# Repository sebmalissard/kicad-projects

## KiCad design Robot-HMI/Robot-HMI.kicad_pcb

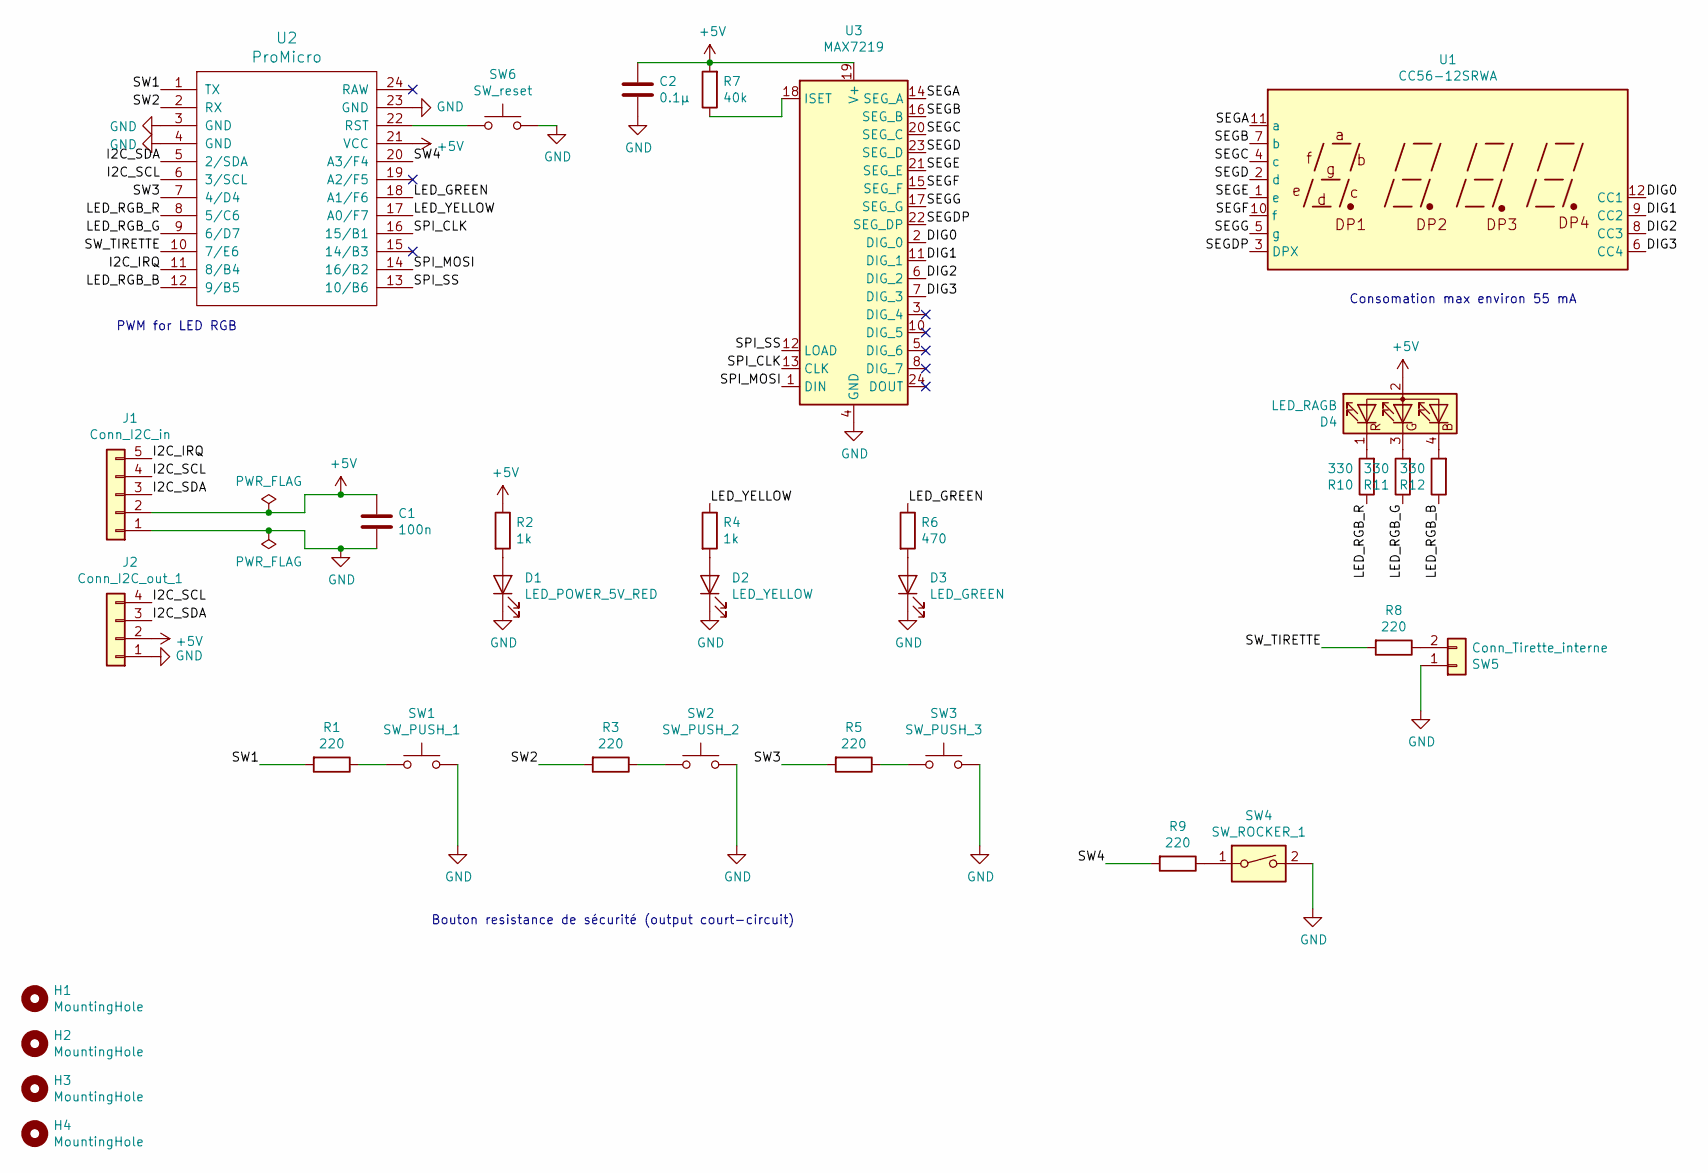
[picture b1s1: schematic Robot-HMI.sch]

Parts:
C1: 100n; C_Disc_D4.3mm_W1.9mm_P5.00mm
C2: 0.1µ; C_Disc_D4.3mm_W1.9mm_P5.00mm
D1: LED_POWER_5V_RED; LED_D5.0mm
D2: LED_YELLOW; LED_D5.0mm
D3: LED_GREEN; LED_D5.0mm
D4: LED_RAGB; LED_D5.0mm-4_RGB_Staggered_Pins
H1, H2, H3, H4: MountingHole; MountingHole_3.2mm_M3
J1: Conn_I2C_in; Molex_SL_171971-0005_1x05_P2.54mm_Vertical
J2: Conn_I2C_out_1; Molex_SL_171971-0004_1x04_P2.54mm_Vertical
R1, R3, R5, R8, R9: 220; R_Axial_DIN0207_L6.3mm_D2.5mm_P7.62mm_Horizontal
R2, R4: 1k; R_Axial_DIN0207_L6.3mm_D2.5mm_P7.62mm_Horizontal
R6: 470; R_Axial_DIN0207_L6.3mm_D2.5mm_P7.62mm_Horizontal
R7: 40k; R_Axial_DIN0207_L6.3mm_D2.5mm_P7.62mm_Horizontal
R10, R11, R12: 330; R_Axial_DIN0207_L6.3mm_D2.5mm_P7.62mm_Horizontal
SW1: SW_PUSH_1; SW_PUSH_12mm_H4.5mm
SW2: SW_PUSH_2; SW_PUSH_12mm_H4.5mm
SW3: SW_PUSH_3; SW_PUSH_12mm_H4.5mm
SW4: SW_ROCKER_1; Molex_SL_70553-0001_1x02_P2.54mm_Horizontal
SW5: Conn_Tirette_interne; Molex_SL_70553-0001_1x02_P2.54mm_Horizontal
SW6: SW_reset; SW_PUSH_6mm_H9.5mm
U1: CC56-12SRWA; CA56-12SRWA
U2: ProMicro
U3: MAX7219; DIP-24_W7.62mm

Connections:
+5V: C1.1, C2.1, D4.2 (A), J1.2, J2.2, R2.1, R7.2, U2.21 (VCC), U3.19 (V+)
/DIG0: U1.12 (CC1), U3.2 (DIG_0)
/DIG1: U1.9 (CC2), U3.11 (DIG_1)
/DIG2: U1.8 (CC3), U3.6 (DIG_2)
/DIG3: U1.6 (CC4), U3.7 (DIG_3)
/I2C_IRQ: J1.5, U2.11 (8/B4)
/I2C_SCL: J1.4, J2.4, U2.6 (3/SCL)
/I2C_SDA: J1.3, J2.3, U2.5 (2/SDA)
/LED_GREEN: R6.1, U2.18 (A1/F6)
/LED_RGB_B: R12.1, U2.12 (9/B5)
/LED_RGB_G: R11.1, U2.9 (6/D7)
/LED_RGB_R: R10.1, U2.8 (5/C6)
/LED_YELLOW: R4.1, U2.17 (A0/F7)
/SEGA: U1.11 (a), U3.14 (SEG_A)
/SEGB: U1.7 (b), U3.16 (SEG_B)
/SEGC: U1.4 (c), U3.20 (SEG_C)
/SEGD: U1.2 (d), U3.23 (SEG_D)
/SEGDP: U1.3 (DPX), U3.22 (SEG_DP)
/SEGE: U1.1 (e), U3.21 (SEG_E)
/SEGF: U1.10 (f), U3.15 (SEG_F)
/SEGG: U1.5 (g), U3.17 (SEG_G)
/SPI_CLK: U2.16 (15/B1), U3.13 (CLK)
/SPI_MOSI: U2.14 (16/B2), U3.1 (DIN)
/SPI_SS: U2.13 (10/B6), U3.12 (LOAD)
/SW1: R1.2, U2.1 (TX)
/SW2: R3.2, U2.2 (RX)
/SW3: R5.2, U2.7 (4/D4)
/SW4: R9.2, U2.20 (A3/F4)
/SW_TIRETTE: R8.2, U2.10 (7/E6)
GND: C1.2, C2.2, D1.1 (K), D2.1 (K), D3.1 (K), J1.1, J2.1, SW1.2, SW2.2, SW3.2, SW4.2, SW5.1, SW6.2, U2.3 (GND), U2.4 (GND), U2.23 (GND), U3.4 (GND), U3.9 (GND)
unnamed: D1.2 (A), R2.2
unnamed: D2.2 (A), R4.2
unnamed: D3.2 (A), R6.2
unnamed: D4.1 (RK), R10.2
unnamed: D4.3 (GK), R11.2
unnamed: D4.4 (BK), R12.2
unnamed: R1.1, SW1.1
unnamed: R3.1, SW2.1
unnamed: R5.1, SW3.1
unnamed: R7.1, U3.18 (ISET)
unnamed: R8.1, SW5.2
unnamed: R9.1, SW4.1
unnamed: SW6.1, U2.22 (RST)

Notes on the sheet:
PWM for LED RGB
Consomation max environ 55 mA
Bouton resistance de sécurité (output court-circuit)

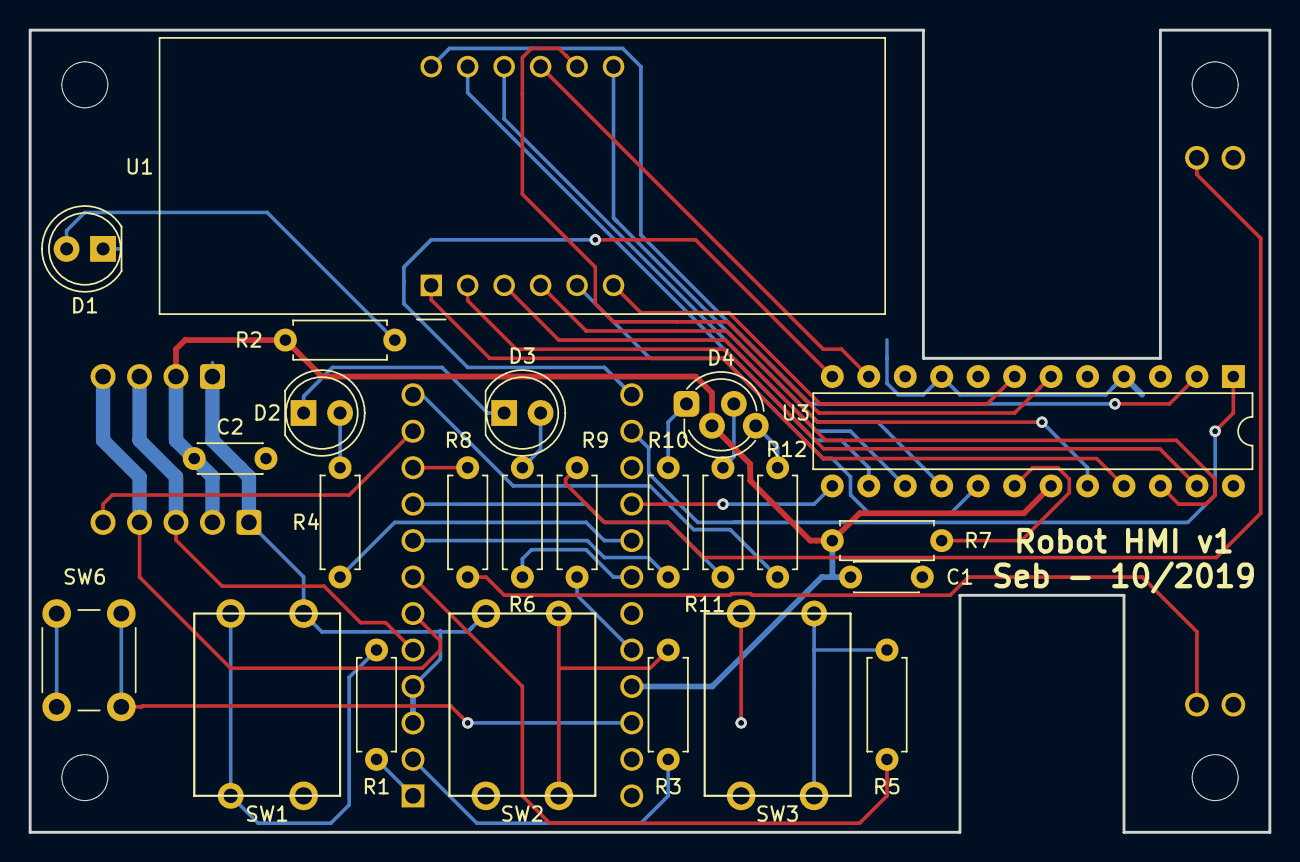
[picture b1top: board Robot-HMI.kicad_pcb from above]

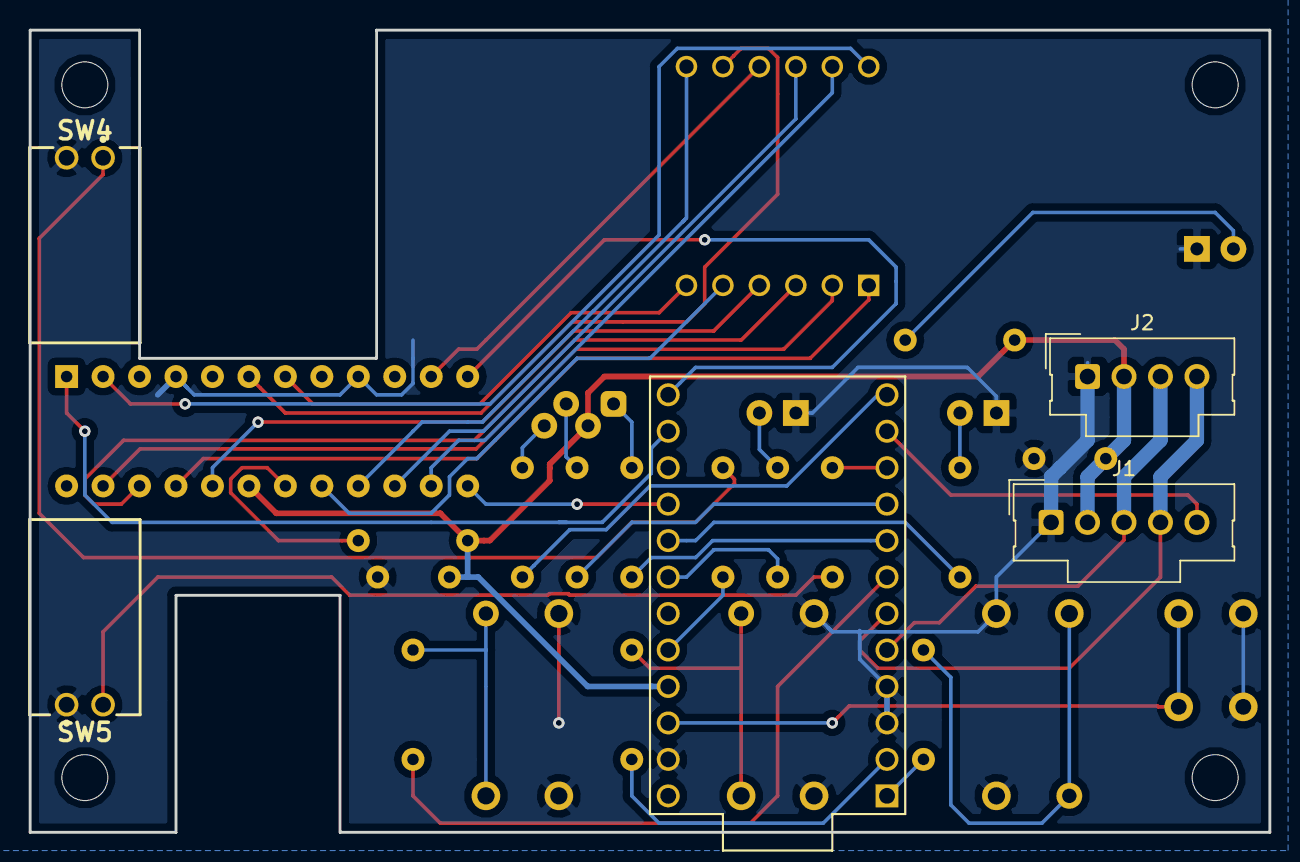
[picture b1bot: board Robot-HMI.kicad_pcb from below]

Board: 2 copper layers, 86.4 x 55.9 mm, 33 parts (5 on the bottom side), 43 nets.

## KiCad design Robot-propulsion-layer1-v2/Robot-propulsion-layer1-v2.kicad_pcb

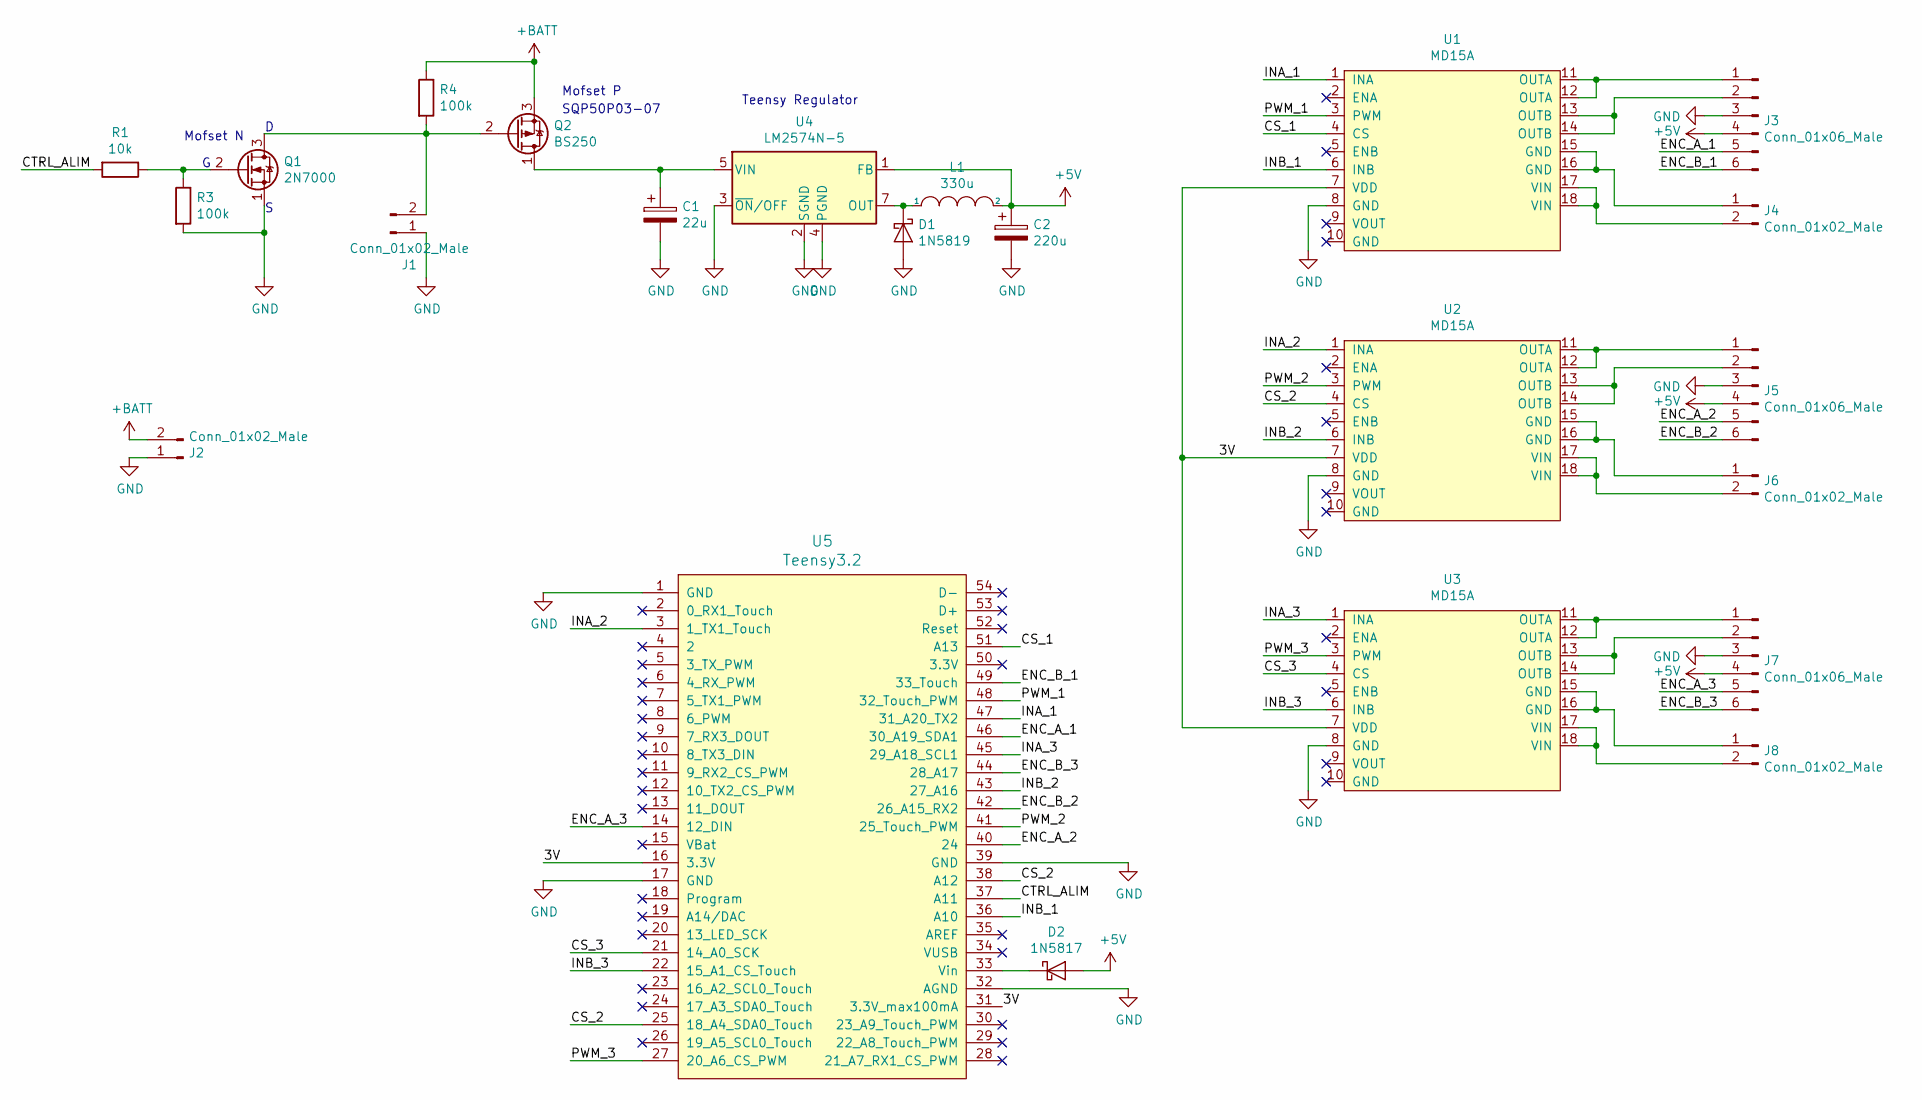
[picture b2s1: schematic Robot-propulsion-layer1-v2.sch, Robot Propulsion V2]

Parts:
C1: 22u; CP_Radial_D4.0mm_P1.50mm
C2: 220u; CP_Radial_D6.3mm_P2.50mm
D1: 1N5819; D_DO-41_SOD81_P10.16mm_Horizontal
D2: 1N5817; D_DO-41_SOD81_P10.16mm_Horizontal
J1, J2, J4, J6, J8: Conn_01x02_Male; PinHeader_1x02_P2.54mm_Vertical
J3, J5, J7: Conn_01x06_Male; PinHeader_1x06_P2.54mm_Horizontal
L1: 330u; L_Radial_D7.8mm_P5.00mm_Fastron_07HCP
Q1: 2N7000; TO-92_Inline
Q2: BS250; TO-220-3_Vertical
R1: 10k; R_Axial_DIN0207_L6.3mm_D2.5mm_P7.62mm_Horizontal
R3, R4: 100k; R_Axial_DIN0207_L6.3mm_D2.5mm_P7.62mm_Horizontal
U1, U2, U3: MD15A
U4: LM2574N-5; DIP-8_W7.62mm
U5: Teensy3.2; Teensy30_31_32_LC

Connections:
+5V: C2.1, D2.2 (A), J3.4, J5.4, J7.4, L1.2, U4.1 (FB)
+BATT: J2.2, Q2.3 (S), R4.1
/3V: U1.7 (VDD), U2.7 (VDD), U3.7 (VDD), U5.16 (3.3V), U5.31 (3.3V_max100mA)
/CS_1: U1.4 (CS), U5.51 (A13)
/CS_2: U2.4 (CS), U5.25 (18_A4_SDA0_Touch), U5.38 (A12)
/CS_3: U3.4 (CS), U5.21 (14_A0_SCK)
/CTRL_ALIM: R1.2, U5.37 (A11)
/ENC_A_1: J3.5, U5.46 (30_A19_SDA1)
/ENC_A_2: J5.5, U5.40 (24)
/ENC_A_3: J7.5, U5.14 (12_DIN)
/ENC_B_1: J3.6, U5.49 (33_Touch)
/ENC_B_2: J5.6, U5.42 (26_A15_RX2)
/ENC_B_3: J7.6, U5.44 (28_A17)
/INA_1: U1.1 (INA), U5.47 (31_A20_TX2)
/INA_2: U2.1 (INA), U5.3 (1_TX1_Touch)
/INA_3: U3.1 (INA), U5.45 (29_A18_SCL1)
/INB_1: U1.6 (INB), U5.36 (A10)
/INB_2: U2.6 (INB), U5.43 (27_A16)
/INB_3: U3.6 (INB), U5.22 (15_A1_CS_Touch)
/PWM_1: U1.3 (PWM), U5.48 (32_Touch_PWM)
/PWM_2: U2.3 (PWM), U5.41 (25_Touch_PWM)
/PWM_3: U3.3 (PWM), U5.27 (20_A6_CS_PWM)
GND: C1.2, C2.2, D1.2 (A), J1.1, J2.1, J3.3, J5.3, J7.3, Q1.1 (S), R3.2, U1.8 (GND), U2.8 (GND), U3.8 (GND), U4.2 (SGND), U4.3 (~ON~/OFF), U4.4 (PGND), U5.1 (GND), U5.17 (GND), U5.32 (AGND), U5.39 (GND)
unnamed: C1.1, Q2.1 (D), U4.5 (VIN)
unnamed: D1.1 (K), L1.1, U4.7 (OUT)
unnamed: D2.1 (K), U5.33 (Vin)
unnamed: J1.2, Q1.3 (D), Q2.2 (G), R4.2
unnamed: J3.1, U1.11 (OUTA), U1.12 (OUTA)
unnamed: J3.2, U1.13 (OUTB), U1.14 (OUTB)
unnamed: J4.1, U1.15 (GND), U1.16 (GND)
unnamed: J4.2, U1.17 (VIN), U1.18 (VIN)
unnamed: J5.1, U2.11 (OUTA), U2.12 (OUTA)
unnamed: J5.2, U2.13 (OUTB), U2.14 (OUTB)
unnamed: J6.1, U2.15 (GND), U2.16 (GND)
unnamed: J6.2, U2.17 (VIN), U2.18 (VIN)
unnamed: J7.1, U3.11 (OUTA), U3.12 (OUTA)
unnamed: J7.2, U3.13 (OUTB), U3.14 (OUTB)
unnamed: J8.1, U3.15 (GND), U3.16 (GND)
unnamed: J8.2, U3.17 (VIN), U3.18 (VIN)
unnamed: Q1.2 (G), R1.1, R3.1

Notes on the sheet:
Teensy Regulator
Mofset N
Mofset P
SQP50P03-07

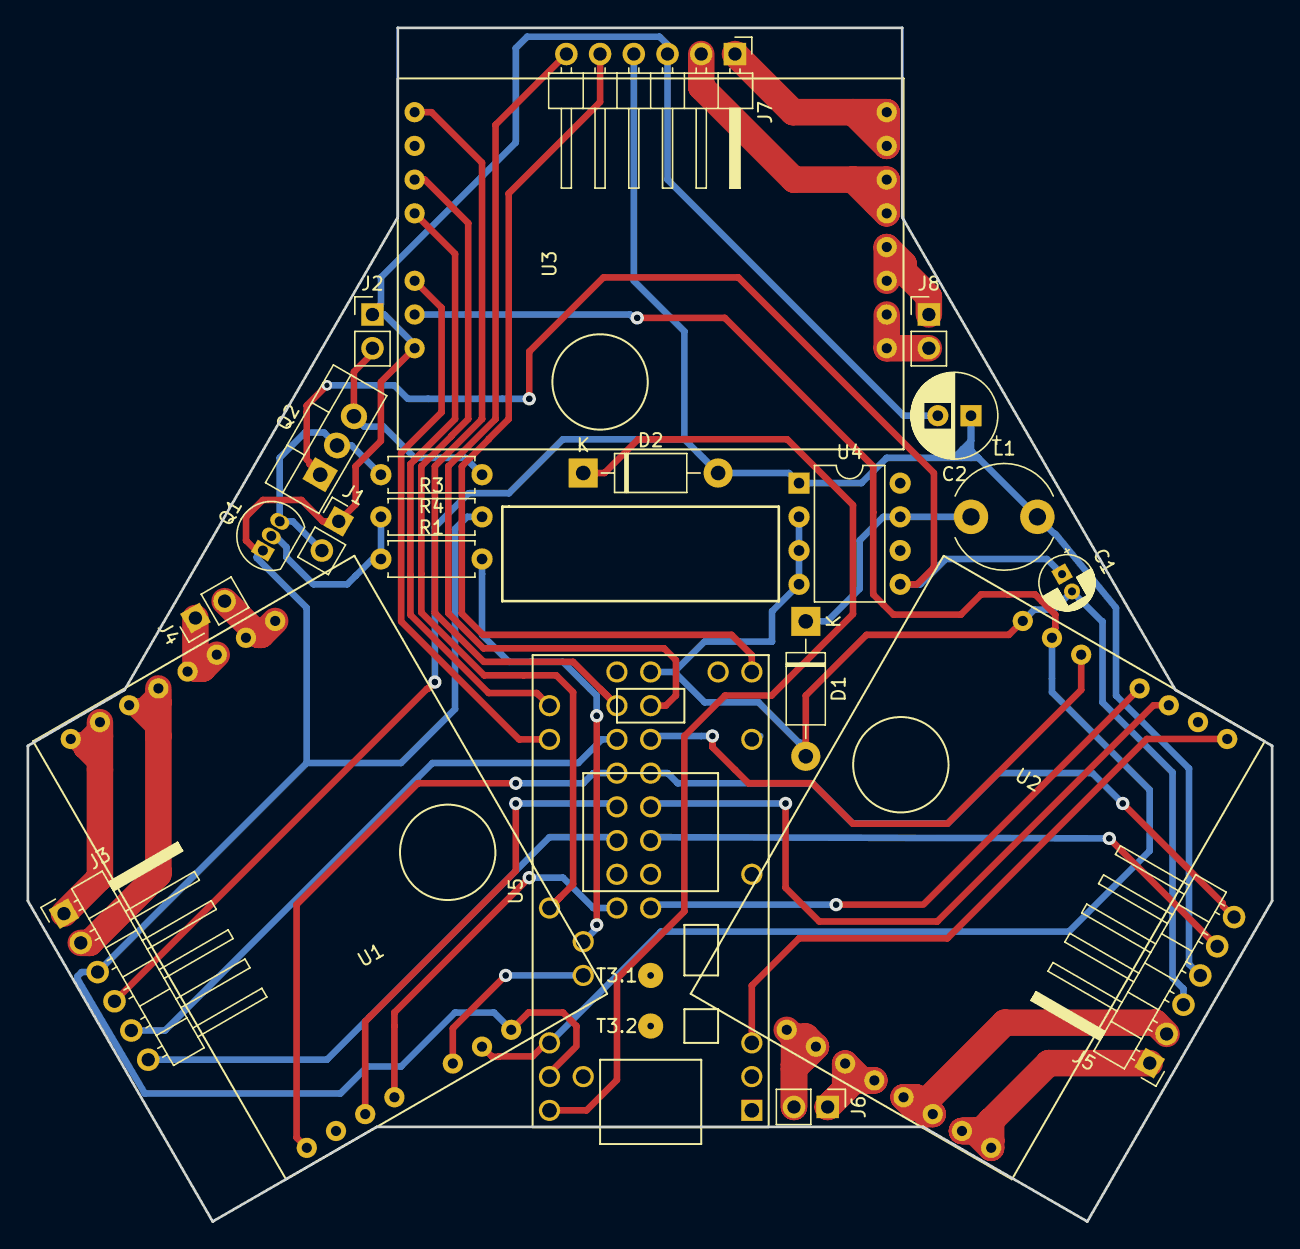
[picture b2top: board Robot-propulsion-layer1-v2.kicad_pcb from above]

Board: 2 copper layers, 93.7 x 89.9 mm, 23 parts (0 on the bottom side), 40 nets.

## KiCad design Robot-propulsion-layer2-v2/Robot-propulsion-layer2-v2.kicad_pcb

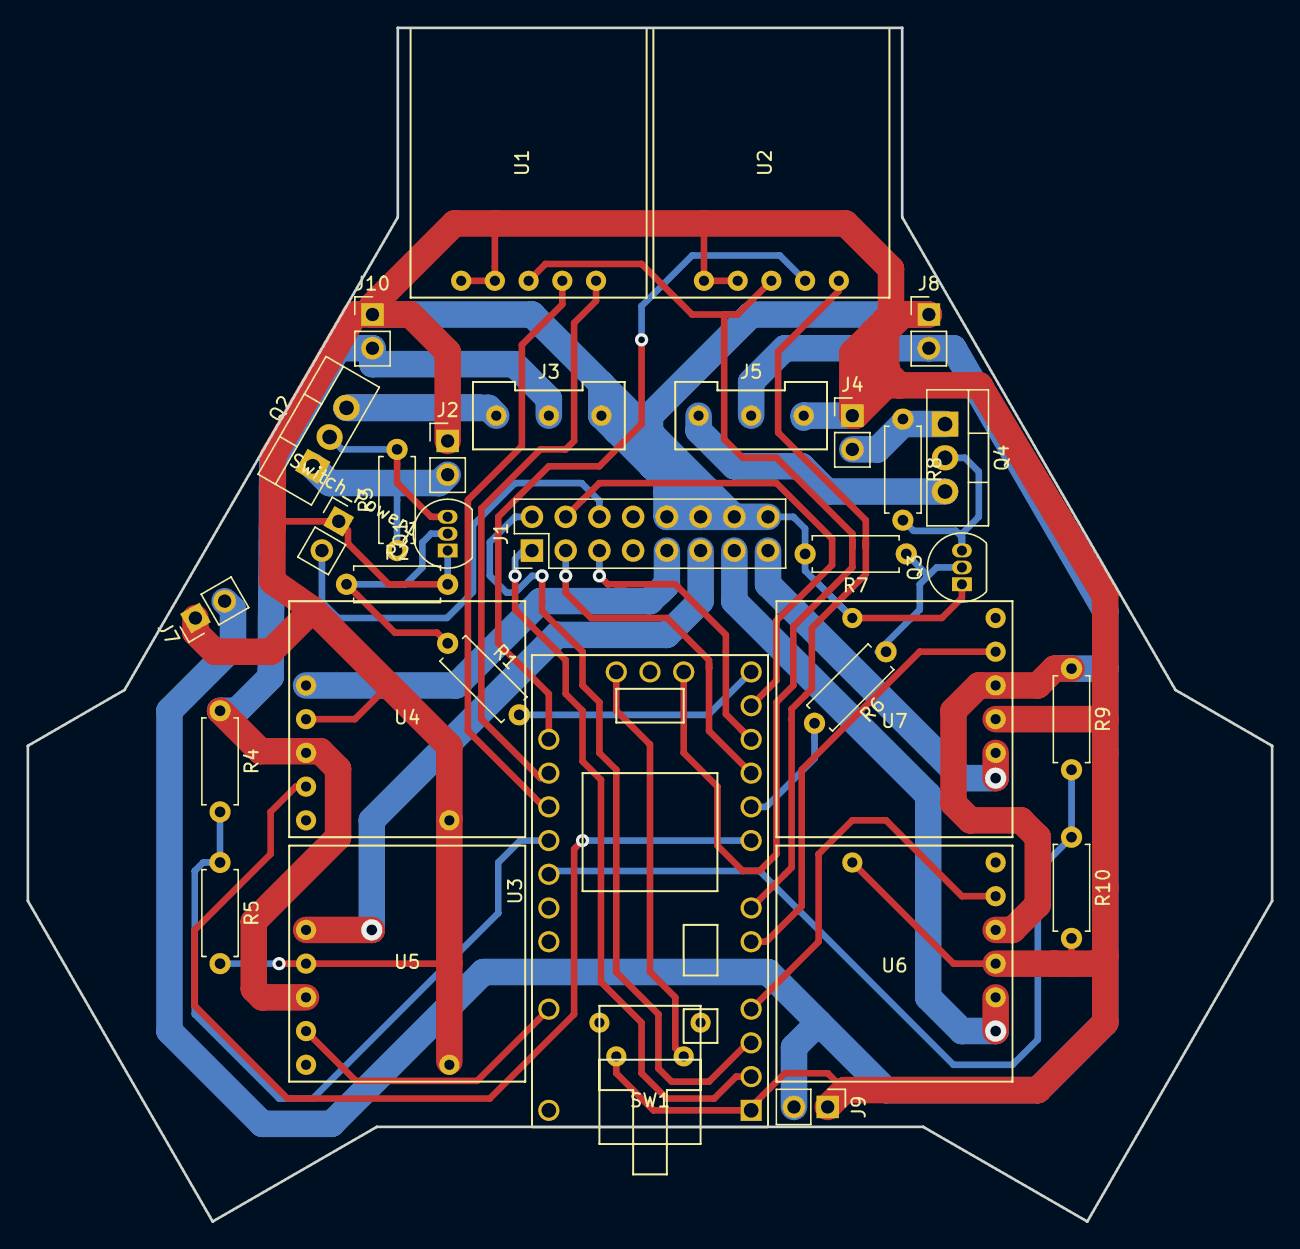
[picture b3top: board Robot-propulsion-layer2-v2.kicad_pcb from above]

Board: 2 copper layers, 93.7 x 89.9 mm, 32 parts (0 on the bottom side), 35 nets.

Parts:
J1: Conn_02x08_Odd_Even; PinHeader_2x08_P2.54mm_Vertical
J2, J4, J7, J8, J9, J10: Conn_01x02_Female; PinHeader_1x02_P2.54mm_Vertical
J3, J5: Conn_01x03_Male; pin_header_3.96
Q1, Q3: 2N7000; TO-92_Inline
Q2, Q4: BS250; TO-220-3_Vertical
R1, R6: 10k; R_Axial_DIN0207_L6.3mm_D2.5mm_P7.62mm_Horizontal
R2, R7: 100k; R_Axial_DIN0207_L6.3mm_D2.5mm_P7.62mm_Horizontal
R3, R4, R5, R8, R9, R10: R; R_Axial_DIN0207_L6.3mm_D2.5mm_P7.62mm_Horizontal
SW1: SW_Push; switch_teensy
Switch_Power1: Conn_01x02_Female; PinHeader_1x02_P2.54mm_Vertical
U1, U2: Current; current
U3: Teensy3.2; Teensy30_31_32_LC_robot_prop_2
U4, U5, U6, U7: Regulator; regulator

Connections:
+3V3: U1.3, U2.3, U3.16
+6V: J3.2, J10.2, R4.1, U4.3, U5.3
+12V: J5.2, J7.2, J8.2, J9.2, R9.1, U6.3, U7.3
/3_3V: J1.9, U4.5
/5V: J1.11, U5.5
/6V: J1.13, U6.5
/9V: J1.15, U7.5
/ALERT_6V: U1.1, U3.23
/ALERT_12V: U2.1, U3.7
/CUR_6V: U1.2, U3.24
/CUR_12V: U2.2, U3.22
/EN_3_3V: U3.9, U4.2
/EN_5V: U3.30, U5.2
/EN_6V: U3.4, U6.2
/EN_9V: U3.6, U7.2
/EN_BAT_6V: R1.2, U3.14
/EN_BAT_12V: R6.2, U3.10
/LED_1: J1.4, U3.13
/LED_2: J1.3, U3.11
/RX: J1.1, U3.2
/STOP_BAT_POWER: J1.5, U3.12
/TX: J1.2, U3.3
/T_6V: R4.2, R5.1, U3.25
/T_12V: R9.2, R10.1, U3.26
GND: J1.10, J1.12, J1.14, J1.16, J2.1, J3.3, J4.1, J5.3, J7.1, J8.1, J9.1, J10.1, Q1.1, Q3.1, R2.2, R5.2, R7.2, R10.2, SW1.2, Switch_Power1.1, U1.4, U1.5, U2.4, U2.5, U3.1, U4.4, U4.6, U5.4, U5.6, U6.4, U6.6, U7.4, U7.6
unnamed: J1.6, Switch_Power1.2
unnamed: J2.2, Q2.1, R3.1
unnamed: J3.1, Q2.3
unnamed: J4.2, Q4.1, R8.1
unnamed: J5.1, Q4.3
unnamed: Q1.2, R1.1, R2.1
unnamed: Q1.3, Q2.2, R3.2
unnamed: Q3.2, R6.1, R7.1
unnamed: Q3.3, Q4.2, R8.2
unnamed: SW1.1, U3.18
